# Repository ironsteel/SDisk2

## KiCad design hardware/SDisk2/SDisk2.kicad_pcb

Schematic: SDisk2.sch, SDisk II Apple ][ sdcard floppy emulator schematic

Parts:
C1, C3: 100uf; CP_Radial_D5.0mm_P2.00mm
C2, C6, C7: 1n; C_Disc_D3.0mm_W1.6mm_P2.50mm
C4, C5: 22p; C_Disc_D3.0mm_W1.6mm_P2.50mm
D1: LED; LED_D3.0mm
DS1: WH1602B-TMI-CT#; PinHeader_1x16_P2.54mm_Vertical
J1: SD_Card; attend-104d-tca0-r06-sdcard-holder
J2: To Apple II DISK controller; PinHeader_2x10_P2.54mm_Horizontal
R1, R5, R6, R7, R9, R12: 10k; R_Axial_DIN0204_L3.6mm_D1.6mm_P5.08mm_Horizontal
R2: 1k5; R_Axial_DIN0204_L3.6mm_D1.6mm_P5.08mm_Horizontal
R3: 470; R_Axial_DIN0204_L3.6mm_D1.6mm_P5.08mm_Horizontal
R4: 270; R_Axial_DIN0204_L3.6mm_D1.6mm_P5.08mm_Horizontal
R8: 330; R_Axial_DIN0204_L3.6mm_D1.6mm_P5.08mm_Horizontal
R10, R11: 100k; R_Axial_DIN0204_L3.6mm_D1.6mm_P5.08mm_Horizontal
SW1: BTN_UP; SW_PUSH_6mm
SW2: BTN_ENTER; SW_PUSH_6mm
SW3: BTN_DOWN; SW_PUSH_6mm
U1: 74LS125; DIP-14_W7.62mm
U2: ATmega328P-PU; DIP-28_W7.62mm
U3: LM317_SOT-223; TO-220-3_Vertical
Y1: 25Mhz; Crystal_HC49-4H_Vertical

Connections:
+5V: C1.1, C2.1, C6.2, C7.2, DS1.2, DS1.15, J2.12, R1.1, R5.2, R6.1, R7.1, R9.1, R12.2, U1.9, U1.10, U1.12, U1.13, U1.14, U2.7 (VCC), U2.20 (AVCC), U2.21 (AREF), U3.3 (VI)
/3.3V: C3.1, J1.4 (VDD), R4.1, U3.2 (VO)
/BTN_DOWN: R9.2, SW3.1 (A), U2.13 (PD7)
/BTN_ENTER: R7.2, SW2.1 (A), U2.12 (PD6)
/BTN_UP: R6.2, SW1.1 (A), U2.19 (PB5)
/DRIVE_EN: J2.14, U1.1, U1.4, U2.23 (PC0)
/LCD_D4: DS1.11, U1.2, U2.24 (PC1)
/LCD_D5: DS1.12, U1.5, U2.26 (PC3)
/LCD_E: DS1.6, U2.28 (PC5)
/LCD_RS: DS1.4, U2.27 (PC4)
/RD_PULSE: J2.16, R10.1, U1.3
/SD_CLK: DS1.14, J1.5 (CLK), U2.11 (PD5)
/SD_CS: J1.1 (CD/DAT3), U2.3 (PD1)
/SD_DI: DS1.13, J1.2 (CMD), U2.6 (PD4)
/SD_DO: J1.7 (DAT0), U2.2 (PD0)
/SD_SW: J1.10 (CARD_DETECT), R1.2, U2.5 (PD3)
/STEP0: J2.2, U2.14 (PB0)
/STEP1: J2.4, U2.15 (PB1)
/STEP2: J2.6, U2.16 (PB2)
/STEP3: J2.8, U2.17 (PB3)
/WRITE: J2.18, U2.25 (PC2)
/W_PROTECT: J2.20, R11.1, U1.6
/W_REQUEST: J2.10, R12.1, U2.4 (PD2)
GND: C1.2, C2.2, C3.2, C4.1, C5.1, C6.1, C7.1, D1.1 (K), DS1.1, DS1.5, DS1.16, J1.3 (GND), J1.6 (GND), J1.13 (GND), J2.1, R2.2, R3.2, R10.2, R11.2, SW1.2 (B), SW2.2 (B), SW3.2 (B), U1.7, U2.8 (GND), U2.22 (GND)
unnamed: C4.2, U2.9 (XTAL1/PB6), Y1.1
unnamed: C5.2, U2.10 (XTAL2/PB7), Y1.2
unnamed: D1.2 (A), R8.1
unnamed: DS1.3, R2.1
unnamed: R3.1, R4.2, U3.1 (ADJ)
unnamed: R5.1, U2.1 (~RESET~/PC6)
unnamed: R8.2, U2.18 (PB4)

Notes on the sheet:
Pins 6, 11, 24, 26 are multiplexed between the SD card, the LCD display and the inputs to the 74LS125 buffer
NOTE/WARNING

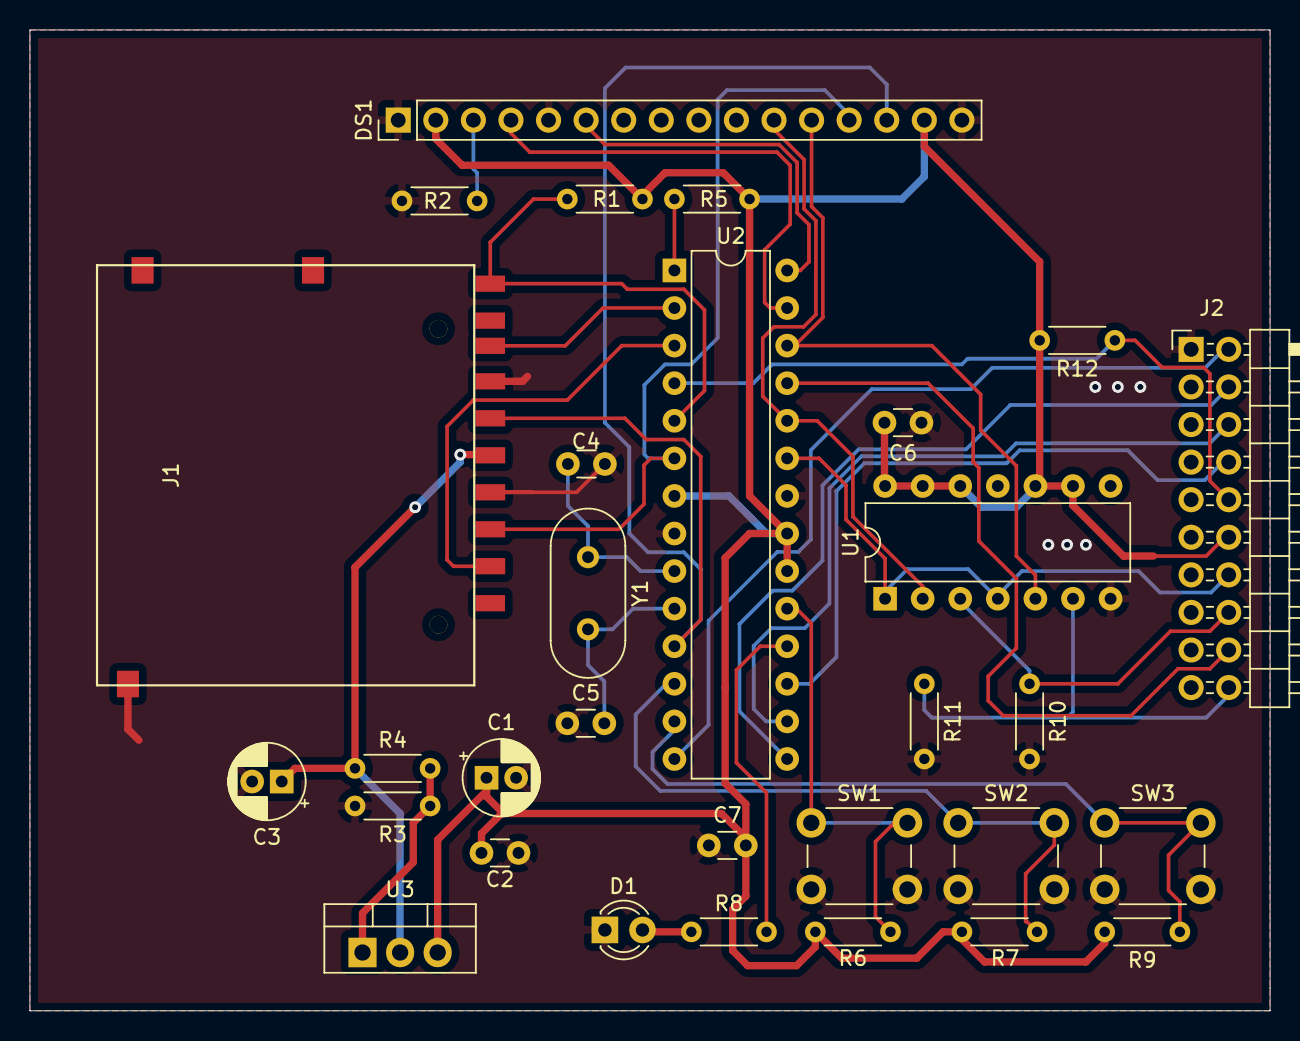
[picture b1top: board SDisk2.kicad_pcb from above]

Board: 2 copper layers, 83.8 x 66.3 mm, 30 parts (0 on the bottom side), 31 nets.

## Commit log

2021-01-30 Associate footprints for most of the components
    Need to create footprints for sdcard holder and LCD display
2021-01-30 Add KiCad project with initial SDisk2 schematic
2021-01-30 Add SDCard footprint and datasheet
2021-01-30 Move all symbols into the SDisk2 project specific library
2021-01-30 Minor tweaks to PCB
2021-01-30 Add datasheet for LCD display
2021-01-30 Tidy up footprint references and values
2021-01-30 Update fp-info-cache
2021-01-30 Initial PCB place and route
2021-01-30 Move symbols to project specific symbol library
2021-01-30 Create netlist and begin place and route
2021-01-30 Add .gitignore
    Remove ignored files
2021-01-30 Add interactive bom for easier assembly by hand
2021-01-30 WIP place and route
2021-01-30 Completely new place and route of PCB
2021-01-30 add a Makefile
2021-01-30 Fix linker errors
2021-01-30 Remove ._ files created by MacOS

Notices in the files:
hardware/SDisk2/SDisk2.sch:
(c) 2010 Koichi NISHIDA
